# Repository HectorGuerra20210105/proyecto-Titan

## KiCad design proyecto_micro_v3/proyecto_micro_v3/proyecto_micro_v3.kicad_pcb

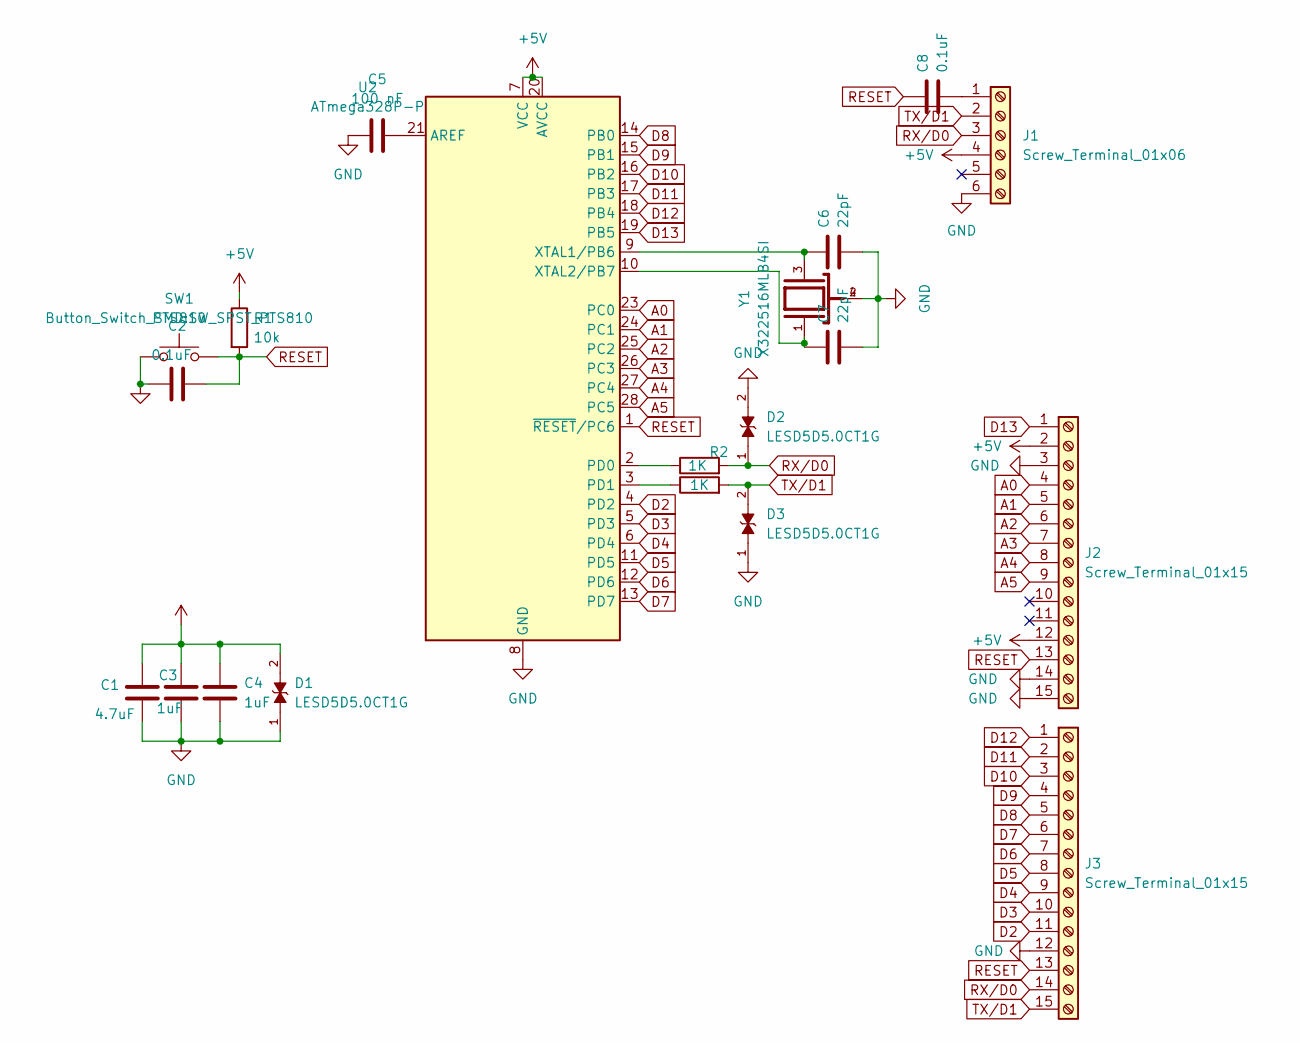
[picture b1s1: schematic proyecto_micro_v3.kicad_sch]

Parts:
C1: 4.7uF; C_0402_1005Metric; LCSC C23733
C2, C8: 0.1uF; C_0402_1005Metric; LCSC C1525
C3, C4: 1uF; C_0402_1005Metric; LCSC C52923
C5: 100 nF; C_0402_1005Metric; LCSC C1525
C6, C7: 22pF; C_0402_1005Metric; LCSC C1555
D1, D2, D3: LESD5D5.0CT1G; TVS_LESD5D5.0CT1G; PARTREV O; LCSC C383211
J1: Screw_Terminal_01x06; PinHeader_1x06_P2.54mm_Vertical
J2, J3: Screw_Terminal_01x15; PinHeader_1x15_P2.54mm_Vertical
R1: 10k; R_0402_1005Metric; LCSC C25744
R2, R3: 1K; R_0402_1005Metric; LCSC C11702
SW1: PTS810; SW_SPST_PTS810; LCSC C116501
U2: ATmega328P-P; DIP-28_W7.62mm
Y1: X322516MLB4SI; Crystal_SMD_SeikoEpson_TSX3225-4Pin_3.2x2.5mm; PARTREV N/A; LCSC C13738

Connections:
+5V: C1.1, C3.1, C4.1, D1.2, J1.4, J2.2, J2.12, R1.1, U2.7 (VCC), U2.20 (AVCC)
A0: J2.4, U2.23 (PC0)
A1: J2.5, U2.24 (PC1)
A2: J2.6, U2.25 (PC2)
A3: J2.7, U2.26 (PC3)
A4: J2.8, U2.27 (PC4)
A5: J2.9, U2.28 (PC5)
D2: J3.11, U2.4 (PD2)
D3: J3.10, U2.5 (PD3)
D4: J3.9, U2.6 (PD4)
D5: J3.8, U2.11 (PD5)
D6: J3.7, U2.12 (PD6)
D7: J3.6, U2.13 (PD7)
D8: J3.5, U2.14 (PB0)
D9: J3.4, U2.15 (PB1)
D10: J3.3, U2.16 (PB2)
D11: J3.2, U2.17 (PB3)
D12: J3.1, U2.18 (PB4)
D13: J2.1, U2.19 (PB5)
GND: C1.2, C2.1, C3.2, C4.2, C5.1, C6.2, C7.2, D1.1, D2.2, D3.1, J1.6, J2.3, J2.14, J2.15, J3.12, SW1.1, U2.8 (GND), U2.22 (GND), Y1.2, Y1.4
unnamed: C8.2, J1.1
unnamed: C5.2, U2.21 (AREF)
unnamed: R2.1, U2.2 (PD0)
unnamed: R3.1, U2.3 (PD1)
unnamed: C6.1, U2.9 (XTAL1/PB6), Y1.3
unnamed: C7.1, U2.10 (XTAL2/PB7), Y1.1
RESET: C2.2, C8.1, J2.13, J3.13, R1.2, SW1.2, U2.1 (~RESET/PC6)
RX/D0: D2.1, J1.3, J3.14, R2.2
TX/D1: D3.2, J1.2, J3.15, R3.2

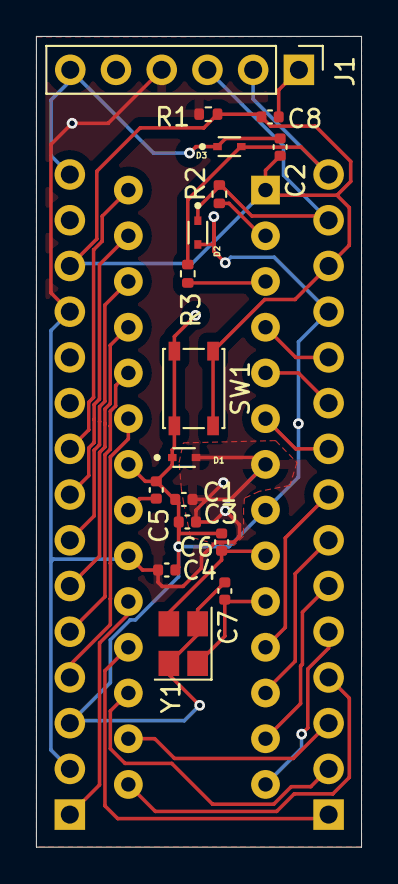
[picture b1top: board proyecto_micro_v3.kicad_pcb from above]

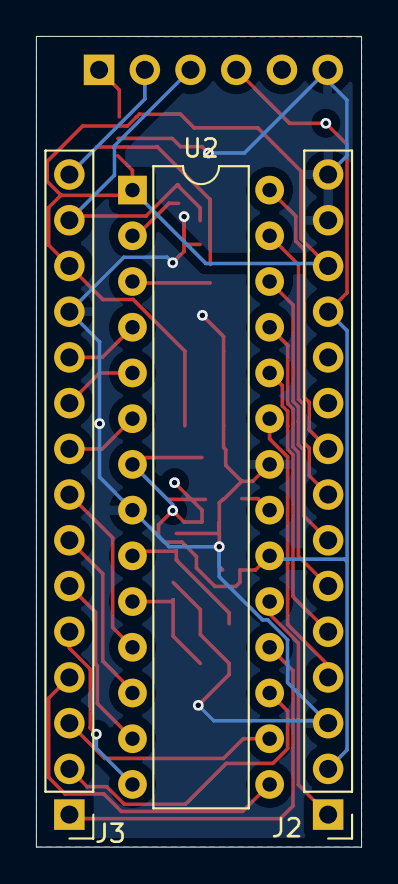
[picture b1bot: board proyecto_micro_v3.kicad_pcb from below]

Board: 2 copper layers, 18.1 x 45.0 mm, 20 parts (3 on the bottom side), 29 nets.

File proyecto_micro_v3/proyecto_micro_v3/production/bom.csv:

Designator,Footprint,Quantity,Value,LCSC Part #
C1,0402,1,4.7uF,C23733
"C2, C8",0402,2,0.1uF,C1525
"C3, C4",0402,2,1uF,C52923
C5,0402,1,100 nF,C1525
"C6, C7",0402,2,22pF,C1555
"D1, D2, D3",TVS_LESD5D5.0CT1G,3,LESD5D5.0CT1G,C383211
J1,PinHeader_1x06_P2.54mm_Vertical,1,Screw_Terminal_01x06,
"J2, J3",PinHeader_1x15_P2.54mm_Vertical,2,Screw_Terminal_01x15,
R1,0402,1,10k,C25744
"R2, R3",0402,2,1K,C11702
SW1,SW_SPST_PTS810,1,PTS810,C116501
U2,DIP-28_W7.62mm,1,ATmega328P-P,
Y1,Crystal_SMD_SeikoEpson_TSX3225-4Pin_3.2x2.5mm,1,X322516MLB4SI,C13738

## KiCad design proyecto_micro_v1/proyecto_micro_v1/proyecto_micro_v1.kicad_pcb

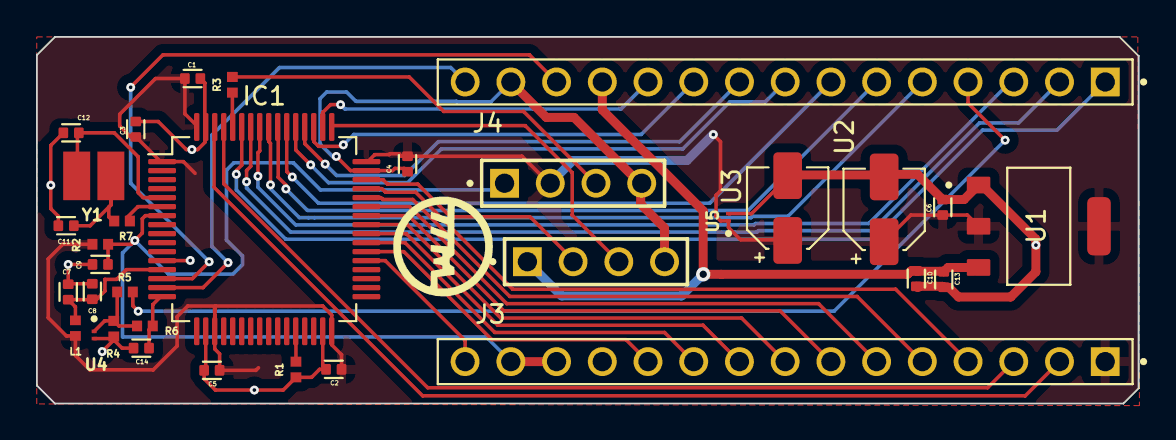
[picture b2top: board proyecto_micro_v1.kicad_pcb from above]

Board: 2 copper layers, 61.2 x 20.4 mm, 34 parts (0 on the bottom side), 39 nets.

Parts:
   : LOGO; tita_v0
C1, C2, C3, C4, C5, C7, C9, C10, C11, C12, C14: 100nF; CAPC1005X55N
C6: 4.7uF; CAPC1005X55N
C8: 1uF; CAPC1005X55N
C13: 10uF; CAPC1005X55N
IC1: STM32F103R8T6; LQFP-64_10x10mm_P0.5mm
J2: SAMTEC_TS-104-G-AA
J2#2: TS-104-G-AA; SAMTEC_TS-104-G-AA
J3, J4: VALCON_V06-1X15-SV-GF-1
L1: 27nH; INDC1005X55N
R1, R2, R3: 10K; RESC1005X40N
R4: 330; RESC1005X40N
R5: 170; RESC1005X40N
R6: 3.5k; RESC1005X40N
R7: 220; RESC1005X40N
U1: AMS1117-3.3; SOT229P700X180-4N
U2, U3: 10uF; CP_Elec_4x5.4
U4, U5: PESD2V0Y1BSFYL; DIO_PESD5V0R1BSFYL
Y1: NX3225GD-8MHZ-STD-CRA-3; XTAL_NX3225GD-8MHZ-STD-CRA-3

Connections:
+3V3: C1.1, C2.1, C3.1, C4.1, C5.1, C6.1, IC1.1 (VBAT), IC1.19 (VDD_4), IC1.32 (VDD_1), IC1.48 (VDD_2), IC1.64 (VDD_3), J2.02, J3.1, L1.1, R2.2, U1.2 (VOUT), U1.4, U2.1, U3.1, U5.1
+5V: C10.1, C13.1, J2#2.01, J4.12, U1.3 (VIN)
ADC: J4.4, R5.2
ADC_0: C14.1, IC1.16 (PA2), R6.1
BOOT _0: IC1.60 (BOOT0), R3.1
GND: C1.2, C2.2, C3.2, C4.2, C5.2, C6.2, C7.2, C8.2, C9.2, C10.2, C11.2, C12.2, C13.2, C14.2, IC1.12 (VSSA), IC1.18 (VSS_4), IC1.31 (VSS_1), IC1.47 (VSS_2), IC1.63 (VSS_3), J2.04, J2#2.04, J3.12, J4.14, R1.1, R4.1, U1.1 (GND/ADJ), U2.2, U3.2, U4.2, U5.2
LIM_L: IC1.55 (PB3), J4.6
LIM_R: IC1.56 (PB4), J4.5
M_0: IC1.53 (PC12), J4.8
M_1: IC1.54 (PD2), J4.7
NRST: C9.1, IC1.7 (NRST), J2.01, J3.13, J3.14, R2.1
unnamed: C11.1, R7.2, Y1.1
unnamed: IC1.28 (PB2), R1.2
unnamed: J2.03, R3.2
unnamed: R4.2, R5.1, R6.2, U4.1
OSC_IN: C12.1, IC1.5 (PD0_OSC_IN), Y1.2
OSC_OUT: IC1.6 (PD1_OSC_OUT), R7.1
PA0: IC1.14 (PA0-WKUP), J4.13
PA1: IC1.15 (PA1), J4.15
PA8: IC1.41 (PA8), J3.8
PA9: IC1.42 (PA9), J3.7
PA10: IC1.43 (PA10), J3.6
PA11: IC1.44 (PA11), J3.5
PA13: IC1.45 (PA12), J3.4
PB5: IC1.57 (PB5), J4.3
PB6: IC1.58 (PB6), J4.2
PB7: IC1.59 (PB7), J4.1
PB8: IC1.61 (PB8), J3.3
PB9: IC1.62 (PB9), J3.2
PC6: IC1.37 (PC6), J3.15
PC7: IC1.38 (PC7), J3.11
PC8: IC1.39 (PC8), J3.10
PC9: IC1.40 (PC9), J3.9
PC10: IC1.51 (PC10), J4.10
PC11: IC1.52 (PC11), J4.9
RECEPTORA: IC1.50 (PA15), J4.11
SWCLK: IC1.49 (PA14), J2#2.03
SWDIO: IC1.46 (PA13), J2#2.02
VDDA: C7.1, C8.1, IC1.13 (VDDA), L1.2

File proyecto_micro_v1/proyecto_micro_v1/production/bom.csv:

Designator,Footprint,Quantity,Value,LCSC Part #
"C1, C10, C11, C12, C14, C2, C3, C4, C5, C7, C9",CAPC1005X55N,11,100nF,C1525
C13,CAPC1005X55N,1,10uF,C1525
C6,CAPC1005X55N,1,4.7uF,C1525
C8,CAPC1005X55N,1,1uF,C1525
IC1,LQFP-64_10x10mm_P0.5mm,1,STM32F103R8T6,C46034
J1,AMPHENOL_76308-103,1,76308-103,
J2,SAMTEC_TS-104-G-AA,1,TS-104-G-AA,
"J3, J4",VALCON_V06-1X15-SV-GF-1,2,  ,
L1,INDC1005X55N,1,27nH,C76760
"R1, R2, R3",RESC1005X40N,3,10K,C25744
R4,RESC1005X40N,1,330,C25744
R5,RESC1005X40N,1,170,C52923
R6,RESC1005X40N,1,3.5k,C2085341
R7,RESC1005X40N,1,220,C25091
U1,SOT229P700X180-4N,1,AMS1117-3.3,C6186
"U2, U3",CP_Elec_4x5.4,2,10uF,C3343
"U4, U5",DIO_PESD5V0R1BSFYL,2,PESD2V0Y1BSFYL,
Y1,XTAL_NX3225GD-8MHZ-STD-CRA-3,1,NX3225GD-8MHZ-STD-CRA-3,
